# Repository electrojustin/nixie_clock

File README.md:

# "nixie_clock"
A repository holding the PCB files for my Nixie Tube Clock

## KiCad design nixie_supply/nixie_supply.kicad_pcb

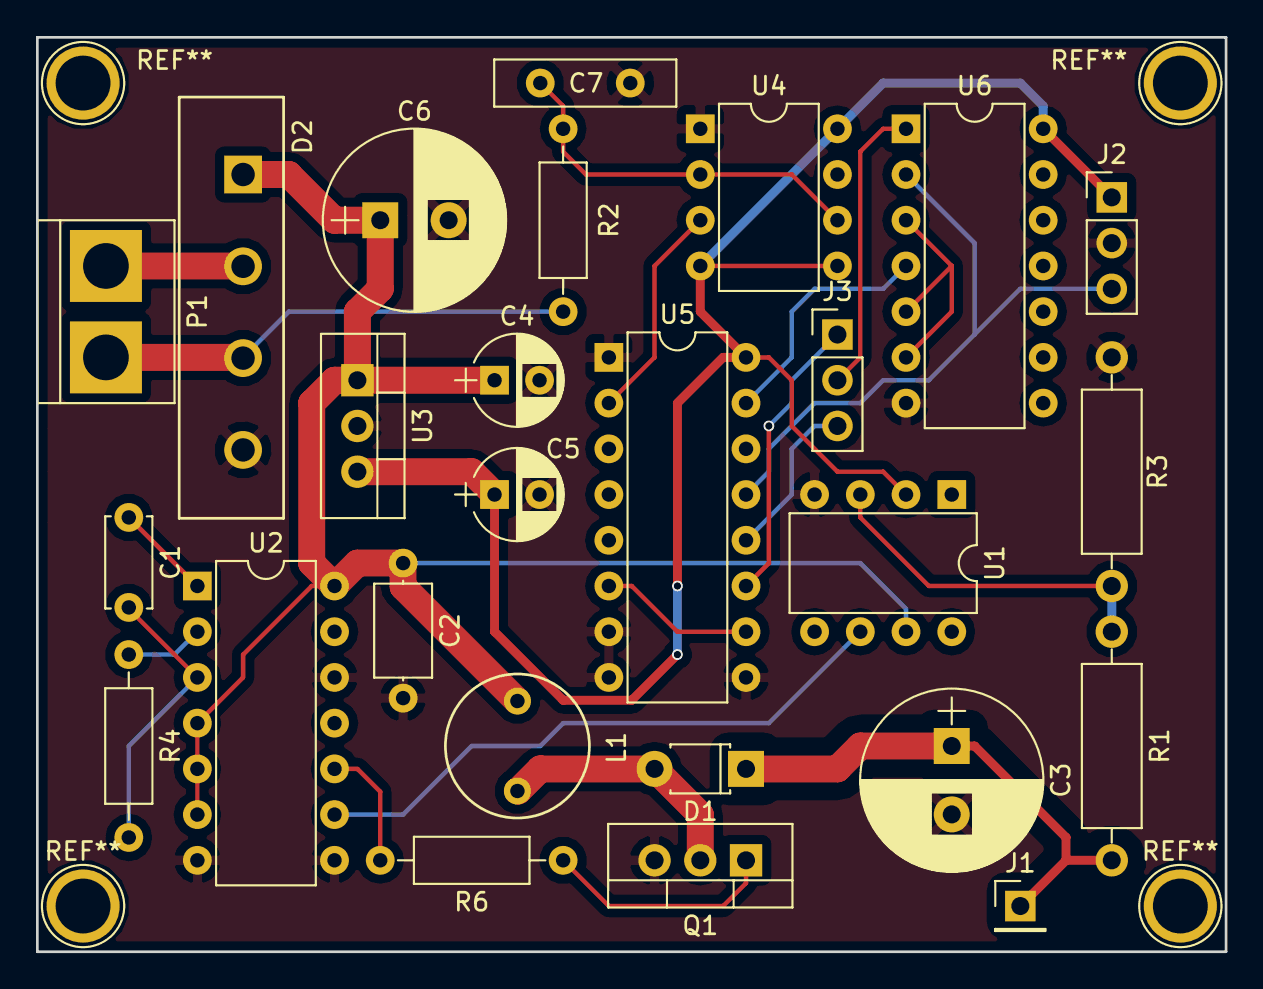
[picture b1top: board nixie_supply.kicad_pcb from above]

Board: 2 copper layers, 66.0 x 50.8 mm, 26 parts (0 on the bottom side), 23 nets.

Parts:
C1: 0.001uF; C_Disc_D5.0mm_W2.5mm_P5.00mm
C2: 0.1uF; C_Axial_L5.1mm_D3.1mm_P7.50mm_Horizontal
C3: 10uF 315V; CP_Radial_D10.0mm_P3.80mm
C4, C5: 10uF; CP_Radial_D5.0mm_P2.50mm
C6: 470uF; CP_Radial_D10.0mm_P3.80mm
C7: 0.1uF; C_Disc_D10.0mm_W2.5mm_P5.00mm
D1: D_HV 400V; D_T-1_P5.08mm_Horizontal
D2: D_Bridge_+AA-; Diode_Bridge_18.5x5.5
J1: CONN_01X01; Pin_Header_Straight_1x01_Pitch2.54mm
J2, J3: CONN_01X03; Pin_Header_Straight_1x03_Pitch2.54mm
L1: 100uH; Neosid_Inductor_Sd8
P1: CONN_01X02; bornier2
Q1: FQPF4N90CT; TO-220_Vertical
R1: 220K; R_Axial_DIN0309_L9.0mm_D3.2mm_P12.70mm_Horizontal_Thick
R2: 1K; R_Axial_DIN0207_L6.3mm_D2.5mm_P10.16mm_Horizontal
R3: 4.7K; R_Axial_DIN0309_L9.0mm_D3.2mm_P12.70mm_Horizontal_Thick
R4: 10K; R_Axial_DIN0207_L6.3mm_D2.5mm_P10.16mm_Horizontal
R6: 120; R_Axial_DIN0207_L6.3mm_D2.5mm_P10.16mm_Horizontal
U1: LM741; DIP-8_W7.62mm
U2: 4047; DIP-14_W7.62mm
U3: 7805; TO-220_Vertical
U4: LM555N; DIP-8_W7.62mm
U5: 4518; DIP-16_W7.62mm
U6: 4011; DIP-14_W7.62mm

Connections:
+5V: C5.1, J2.1, U1.2, U3.3, U4.4, U4.5, U4.8, U5.16, U6.14
+12V: C2.1, C4.1, C6.1, D2.3, L1.1, U1.7, U2.4, U2.5, U2.6, U2.14, U3.1
+12VA: D2.4, P1.2, R2.1
+240V: C3.1, D1.1, J1.1, R1.2
-12VA: D2.2, P1.1
/PPS/CLK_OUT: J2.3, U5.13, U6.2
GND: C2.2, C3.2, C4.2, C5.2, C6.2, C7.2, D2.1, J2.2, Q1.3, R3.2, U1.4, U2.7, U2.8, U2.12, U3.2, U4.1, U5.1, U5.7, U5.8, U5.9, U6.7
unnamed: C1.1, U2.1
unnamed: C1.2, R4.2, U2.3
unnamed: C7.1, R2.2, U4.2, U4.6
unnamed: D1.2, L1.2, Q1.2
unnamed: J3.1, U5.11
unnamed: J3.2, U6.1
unnamed: J3.3, U5.12
unnamed: Q1.1, R6.1
unnamed: R1.1, R3.1, U1.3
unnamed: R4.1, U2.2
unnamed: R6.2, U2.10
unnamed: U1.6, U2.9
unnamed: U4.3, U5.2
unnamed: U5.6, U5.10
unnamed: U5.15, U6.4
unnamed: U6.3, U6.5, U6.6

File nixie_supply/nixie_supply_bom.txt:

Reference, Value, Footprint, Datasheet
"P1","CONN_01X02","",""
"P2","CONN_01X04","",""
"U2","4047","",""
"C1","0.001uF","",""
"R4","10K","",""
"R6","120","",""
"Q1","FQPF4N90CT","TO_220",""
"L1","100uH","",""
"D1","D_HV","",""
"C3","C_HV","",""
"U1","LM741","",""
"R1","220K","",""
"R3","4.7K","",""
"R2","1.2K","",""
"R5","4.7K","",""
"C2","0.1uF","",""
"D2","D_Bridge_+AA-","",""
"C6","220uF","",""
"U3","7805","",""
"C4","10uF","",""
"C5","10uF","",""
"U4","LM741","",""
"U5","4518","",""
"U6","4011","",""

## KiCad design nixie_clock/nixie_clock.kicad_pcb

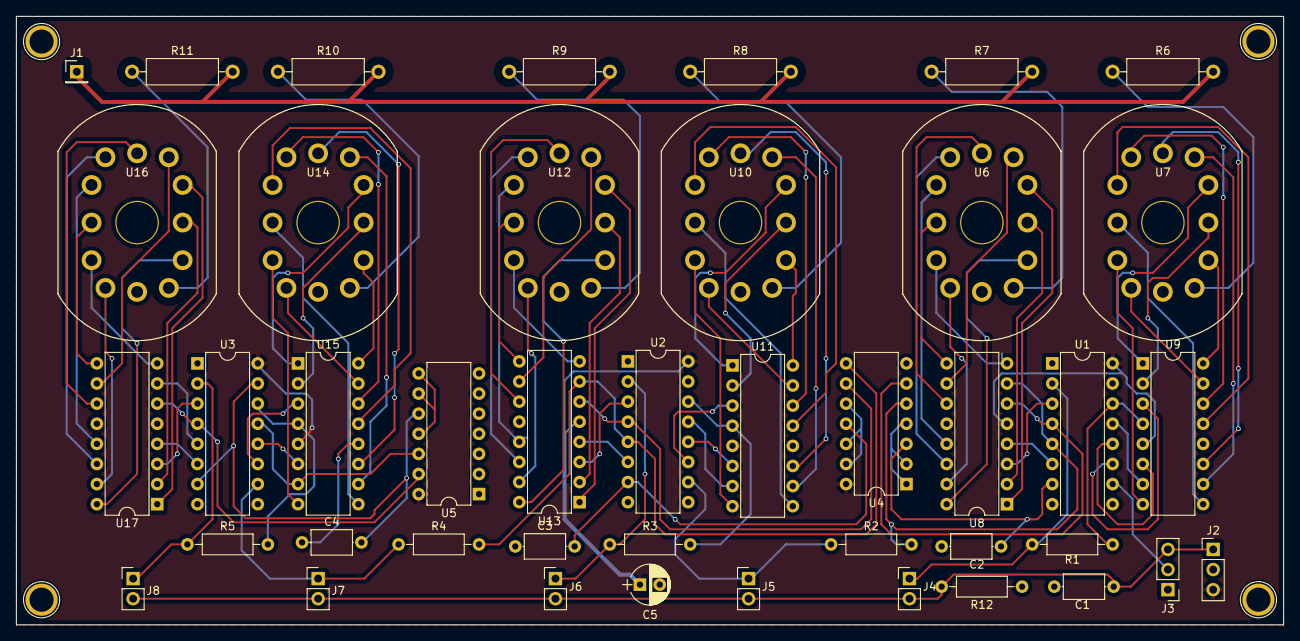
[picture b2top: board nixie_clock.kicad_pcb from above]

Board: 2 copper layers, 160.0 x 76.8 mm, 42 parts (0 on the bottom side), 106 nets.

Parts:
C1, C2, C3, C4: 0.1uF; C_Axial_L5.1mm_D3.1mm_P7.50mm_Horizontal
C5: 10uF; CP_Radial_D5.0mm_P2.50mm
J1: CONN_01X01; Pin_Header_Straight_1x01_Pitch2.54mm
J2, J3: CONN_01X03; Pin_Header_Straight_1x03_Pitch2.54mm
J4, J5, J6, J7, J8: CONN_01X02; Pin_Header_Straight_1x02_Pitch2.54mm
R1, R2, R3, R4, R5: 1K; R_Axial_DIN0207_L6.3mm_D2.5mm_P10.16mm_Horizontal
R6, R7, R8, R9, R10, R11: 33K; R_Axial_DIN0309_L9.0mm_D3.2mm_P12.70mm_Horizontal_Thick
R12: 4.7K; R_Axial_DIN0207_L6.3mm_D2.5mm_P10.16mm_Horizontal
U1, U2, U3: 4518; DIP-16_W7.62mm
U4, U5: 4011; DIP-14_W7.62mm
U6, U7, U10, U12, U14, U16: IN-12; IN12
U8, U9, U11, U13, U15, U17: K155ID1; DIP-16_W7.62mm

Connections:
+5V: C5.1, J2.3, U1.16, U2.16, U3.16, U4.14, U5.14, U8.5, U9.5, U11.5, U13.5, U15.5, U17.5
+240V: J1.1, R6.2, R7.2, R8.2, R9.2, R10.2, R11.2
/1hour/1s: U3.11, U15.3
/1hour/2s: U3.12, U15.6
/1hour/4s: U3.13, U5.12, U15.7
/1hour/8s: R5.2, U3.14, U15.4
/1minute/1s: U2.11, U11.3
/1minute/2s: U2.12, U11.6
/1minute/4s: U2.13, U11.7
/1minute/8s: R3.2, U2.14, U11.4
/1second/1s: U1.11, U9.3
/1second/2s: U1.12, U9.6
/1second/4s: U1.13, U9.7
/1second/8s: R1.2, U1.14, U9.4
/10hour/1s: U3.3, U17.3
/10hour/2s: U3.4, U5.13, U17.6
/10hour/4s: U3.5, U17.7
/10hour/8s: U3.6, U17.4
/10minute/1s: U2.3, U13.3
/10minute/2s: U2.4, U4.9, U13.6
/10minute/4s: R4.2, U2.5, U4.8, U13.7
/10minute/8s: U2.6, U13.4
/10second/1s: U1.3, U8.3
/10second/2s: U1.4, U4.6, U8.6
/10second/4s: R2.2, U1.5, U4.5, U8.7
/10second/8s: U1.6, U8.4
GND: C1.1, C2.1, C3.1, C4.1, C5.2, J2.2, J3.1, R12.2, U1.1, U1.8, U1.9, U1.15, U2.1, U2.8, U2.9, U2.15, U3.1, U3.8, U3.9, U4.7, U5.7, U8.12, U9.12, U11.12, U13.12, U15.12, U17.12
unnamed: C1.2, J2.1, J3.3, J4.2, J5.2, J6.2, J7.2, J8.2, R12.1
unnamed: C2.2, U1.7, U4.3
unnamed: C3.2, U2.7, U4.11
unnamed: C4.2, U3.7, U3.15, U5.10
unnamed: J3.2, U1.10
unnamed: J4.1, R1.1, U1.2
unnamed: J5.1, R2.1, U2.10
unnamed: J6.1, R3.1, U2.2
unnamed: J7.1, R4.1, U3.10
unnamed: J8.1, R5.1, U3.2
unnamed: R6.1, U7.1
unnamed: R7.1, U6.1
unnamed: R8.1, U10.1
unnamed: R9.1, U12.1
unnamed: R10.1, U14.1
unnamed: R11.1, U16.1
unnamed: U4.1, U4.2, U4.4
unnamed: U4.10, U4.12, U4.13
unnamed: U5.8, U5.9, U5.11
unnamed: U6.2, U8.16
unnamed: U6.3, U8.2
unnamed: U6.4, U8.1
unnamed: U6.5, U8.10
unnamed: U6.6, U8.11
unnamed: U6.7, U8.14
unnamed: U6.8, U8.13
unnamed: U6.9, U8.9
unnamed: U6.10, U8.8
unnamed: U6.11, U8.15
unnamed: U7.2, U9.16
unnamed: U7.3, U9.2
unnamed: U7.4, U9.1
unnamed: U7.5, U9.10
unnamed: U7.6, U9.11
unnamed: U7.7, U9.14
unnamed: U7.8, U9.13
unnamed: U7.9, U9.9
unnamed: U7.10, U9.8
unnamed: U7.11, U9.15
unnamed: U10.2, U11.16
unnamed: U10.3, U11.2
unnamed: U10.4, U11.1
unnamed: U10.5, U11.10
unnamed: U10.6, U11.11
unnamed: U10.7, U11.14
unnamed: U10.8, U11.13
unnamed: U10.9, U11.9
unnamed: U10.10, U11.8
unnamed: U10.11, U11.15
unnamed: U12.2, U13.16
unnamed: U12.3, U13.2
unnamed: U12.4, U13.1
unnamed: U12.5, U13.10
unnamed: U12.6, U13.11
unnamed: U12.7, U13.14
unnamed: U12.8, U13.13
unnamed: U12.9, U13.9
unnamed: U12.10, U13.8
unnamed: U12.11, U13.15
unnamed: U14.2, U15.16
unnamed: U14.3, U15.2
unnamed: U14.4, U15.1
unnamed: U14.5, U15.10
unnamed: U14.6, U15.11
unnamed: U14.7, U15.14
unnamed: U14.8, U15.13
unnamed: U14.9, U15.9
unnamed: U14.10, U15.8
unnamed: U14.11, U15.15
unnamed: U16.2, U17.16
unnamed: U16.3, U17.2
unnamed: U16.4, U17.1
unnamed: U16.5, U17.10
unnamed: U16.6, U17.11
unnamed: U16.7, U17.14
unnamed: U16.8, U17.13
unnamed: U16.9, U17.9
unnamed: U16.10, U17.8
unnamed: U16.11, U17.15

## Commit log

2017-05-08 Added supply board
2017-05-08 Library reorganization
2017-05-08 Added display board
2017-05-13 minor cleanups
2017-05-14 Footprint associations
2017-05-14 Power supply layout
2017-05-20 Clock board layout
2017-05-28 Started routing for the clock
2017-05-29 Finished routing
2017-05-29 I had the 10 minute and 1 hour setting connectors mixed up
2017-08-05 Supply board mk2: reduced time base noise, upped some clearances, added ground plane
2017-08-06 Added more noise reduction to clock signal, added top ground plane
2017-08-07 Added more isolation on the HV transient netclass
2017-08-13 Overhaul of clock board. Fixed hour digits, added more noise immunity, reduced height
